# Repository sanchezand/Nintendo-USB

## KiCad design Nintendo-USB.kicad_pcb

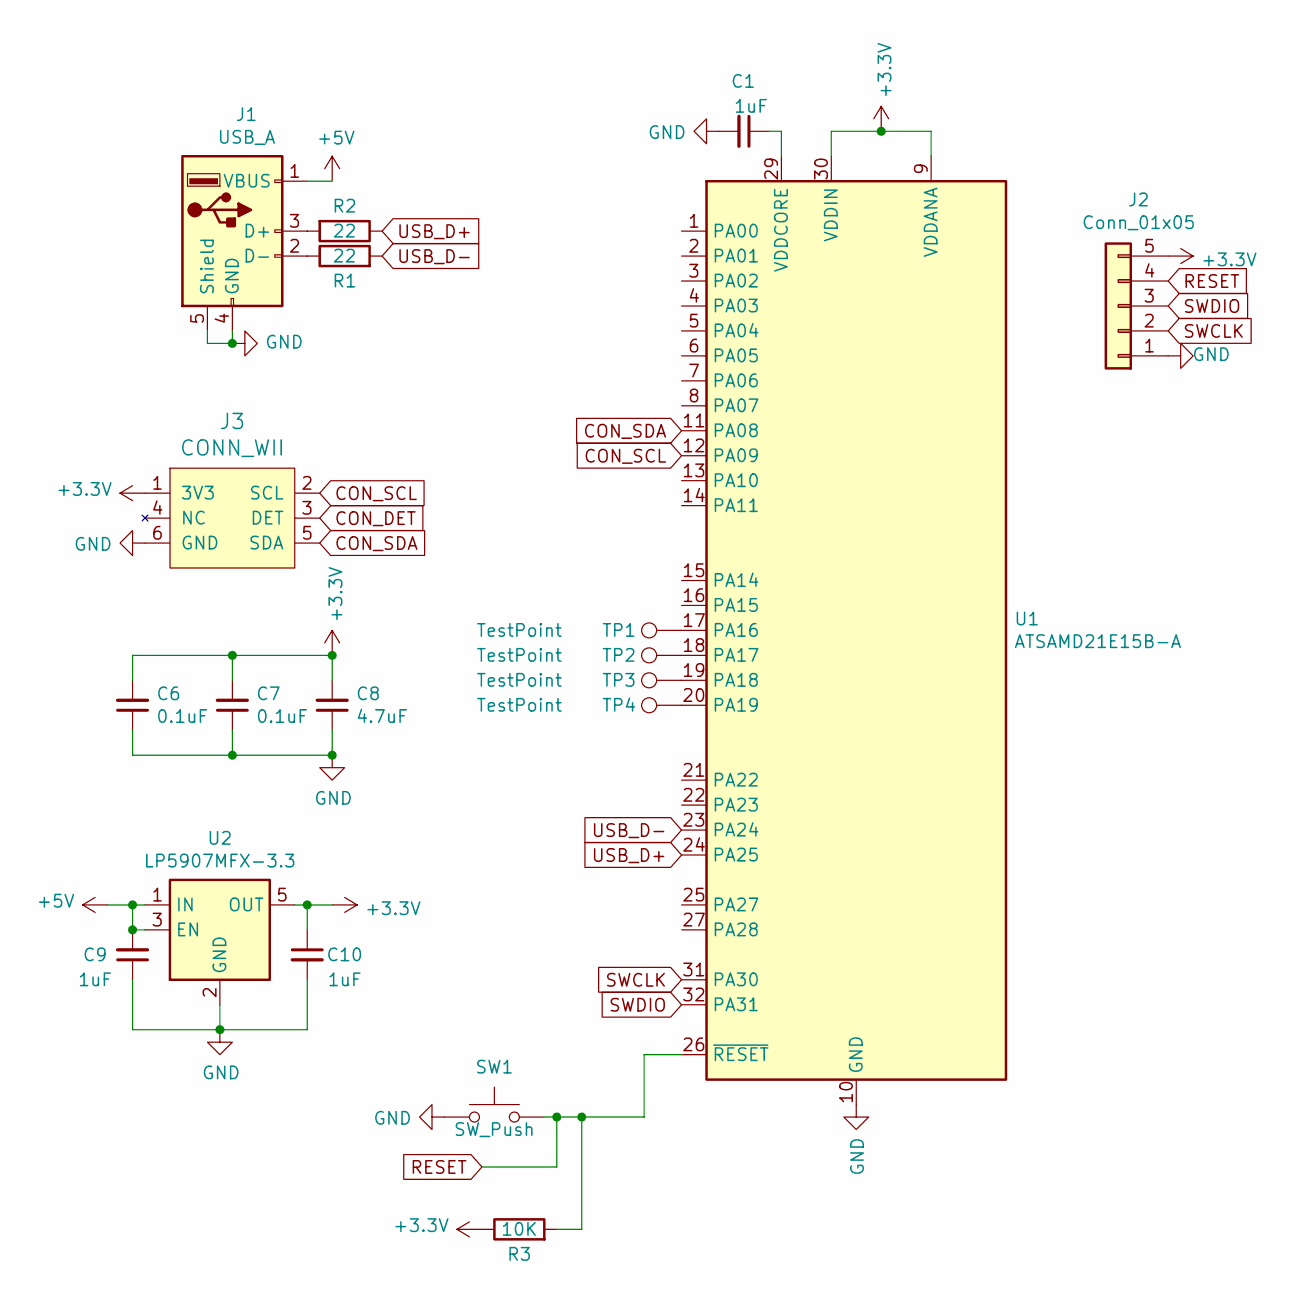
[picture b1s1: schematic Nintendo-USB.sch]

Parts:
C1, C9, C10: 1uF; C_0805_2012Metric_Pad1.18x1.45mm_HandSolder
C6, C7: 0.1uF; C_0805_2012Metric_Pad1.18x1.45mm_HandSolder
C8: 4.7uF; C_0805_2012Metric_Pad1.18x1.45mm_HandSolder
J1: USB_A; SOFNG-USB-07
J2: Conn_01x05; PinHeader_2x03_P2.00mm_Vertical
J3: CONN_WII
R1, R2: 22; R_0805_2012Metric_Pad1.20x1.40mm_HandSolder
R3: 10K; R_0805_2012Metric_Pad1.20x1.40mm_HandSolder
SW1: SW_Push; XKB-TS-1185EC-C-D-B
TP1, TP2, TP3, TP4: TestPoint; TestPoint_Pad_D1.0mm
U1: ATSAMD21E15B-A; TQFP-32_7x7mm_P0.8mm
U2: LP5907MFX-3.3; SOT-23-5

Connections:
+3V3: C6.2, C7.2, C8.2, C10.1, J2.5, J3.1 (3V3), R3.1, U1.9 (VDDANA), U1.30 (VDDIN), U2.5 (OUT)
+5V: C9.2, J1.1 (VBUS), U2.1 (IN), U2.3 (EN)
CON_DET: J3.3 (DET)
CON_SCL: J3.2 (SCL), U1.12 (PA09)
CON_SDA: J3.5 (SDA), U1.11 (PA08)
GND: C1.2, C6.1, C7.1, C8.1, C9.1, C10.2, J1.4 (GND), J1.5 (Shield), J2.1, J3.6 (GND), SW1.1, U1.10 (GND), U1.28 (GND), U2.2 (GND)
unnamed: C1.1, U1.29 (VDDCORE)
unnamed: J1.2 (D-), R1.1
unnamed: J1.3 (D+), R2.2
unnamed: TP1.1, U1.17 (PA16)
unnamed: TP2.1, U1.18 (PA17)
unnamed: TP3.1, U1.19 (PA18)
unnamed: TP4.1, U1.20 (PA19)
RESET: J2.4, R3.2, SW1.2, U1.26 (~RESET)
SWCLK: J2.2, U1.31 (PA30)
SWDIO: J2.3, U1.32 (PA31)
USB_D+: R2.1, U1.24 (PA25)
USB_D-: R1.2, U1.23 (PA24)

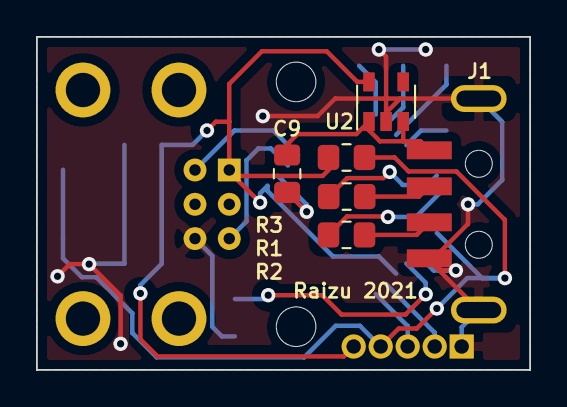
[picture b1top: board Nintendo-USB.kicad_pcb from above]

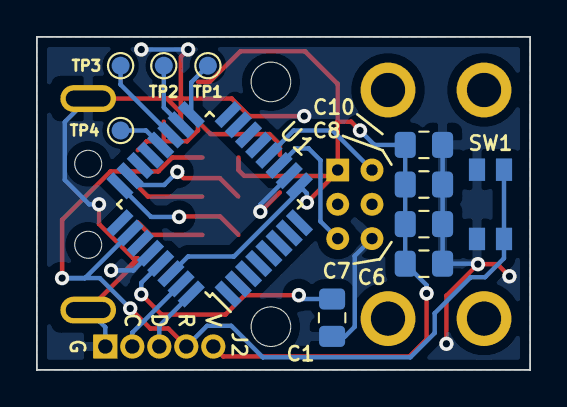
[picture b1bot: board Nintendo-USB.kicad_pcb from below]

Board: 2 copper layers, 27.4 x 18.5 mm, 19 parts (11 on the bottom side), 17 nets.

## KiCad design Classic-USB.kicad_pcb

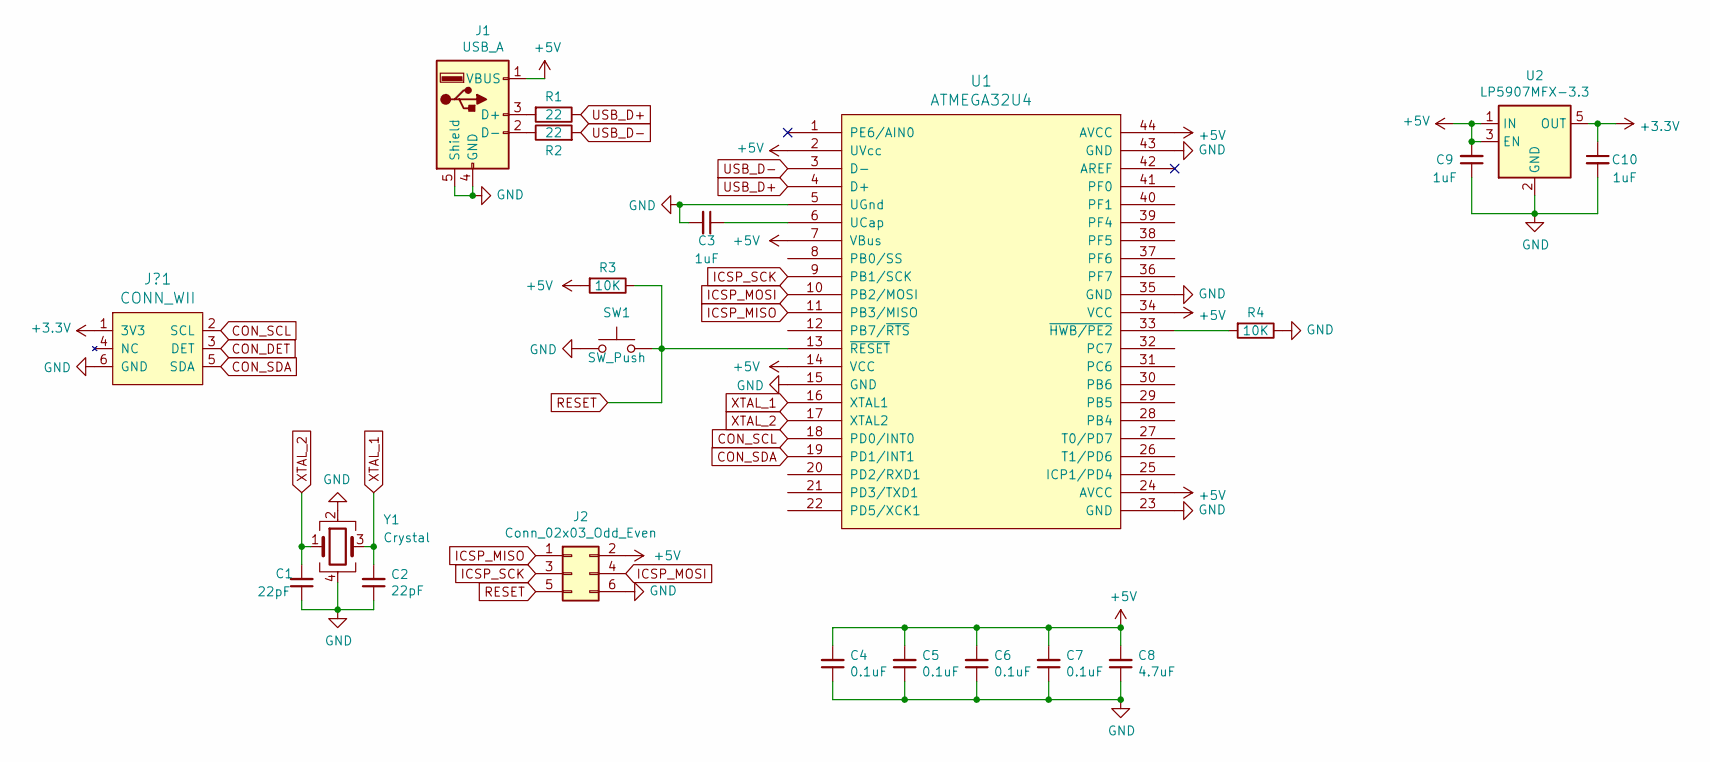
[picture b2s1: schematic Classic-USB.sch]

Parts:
C1, C2: 22pF; C_0805_2012Metric_Pad1.18x1.45mm_HandSolder
C3, C9, C10: 1uF; C_0805_2012Metric_Pad1.18x1.45mm_HandSolder
C4, C5, C6, C7: 0.1uF; C_0805_2012Metric_Pad1.18x1.45mm_HandSolder
C8: 4.7uF; C_0805_2012Metric_Pad1.18x1.45mm_HandSolder
J1: USB_A; SOFNG-USB-07
J2: Conn_02x03_Odd_Even; PinHeader_2x03_P2.54mm_Vertical
J?1: CONN_WII
R1, R2: 22; R_0805_2012Metric_Pad1.20x1.40mm_HandSolder
R3, R4: 10K; R_0805_2012Metric_Pad1.20x1.40mm_HandSolder
SW1: SW_Push; XKB-TS-1185EC-C-D-B
U1: ATMEGA32U4; TQFP-44_10x10mm_P0.8mm
U2: LP5907MFX-3.3; SOT-23-5
Y1: Crystal; Crystal_SMD_SeikoEpson_FA238-4Pin_3.2x2.5mm

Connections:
+3V3: C10.1, J?1.1 (3V3), U2.5 (OUT)
+5V: C4.2, C5.2, C6.2, C7.2, C8.2, C9.2, J1.1 (VBUS), J2.2, R3.2, U1.2 (UVcc), U1.7 (VBus), U1.14 (VCC), U1.24 (AVCC), U1.34 (VCC), U1.44 (AVCC), U2.1 (IN), U2.3 (EN)
CON_DET: J?1.3 (DET)
CON_SCL: J?1.2 (SCL), U1.18 (PD0/INT0)
CON_SDA: J?1.5 (SDA), U1.19 (PD1/INT1)
GND: C1.1, C2.1, C3.2, C4.1, C5.1, C6.1, C7.1, C8.1, C9.1, C10.2, J1.4 (GND), J1.5 (Shield), J2.6, J?1.6 (GND), R4.1, SW1.1, U1.5 (UGnd), U1.15 (GND), U1.23 (GND), U1.35 (GND), U1.43 (GND), U2.2 (GND), Y1.2, Y1.4
ICSP_MISO: J2.1, U1.11 (PB3/MISO)
ICSP_MOSI: J2.4, U1.10 (PB2/MOSI)
ICSP_SCK: J2.3, U1.9 (PB1/SCK)
unnamed: C3.1, U1.6 (UCap)
unnamed: J1.2 (D-), R2.1
unnamed: J1.3 (D+), R1.2
unnamed: R4.2, U1.33 (~HWB/PE2)
RESET: J2.5, R3.1, SW1.2, U1.13 (~RESET)
USB_D+: R1.1, U1.4 (D+)
USB_D-: R2.2, U1.3 (D-)
XTAL_1: C2.2, U1.16 (XTAL1), Y1.3
XTAL_2: C1.2, U1.17 (XTAL2), Y1.1

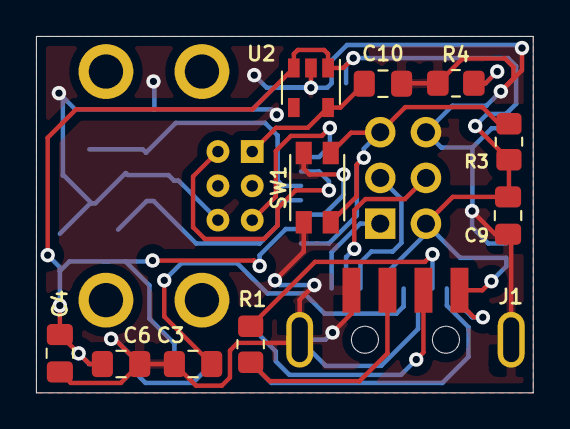
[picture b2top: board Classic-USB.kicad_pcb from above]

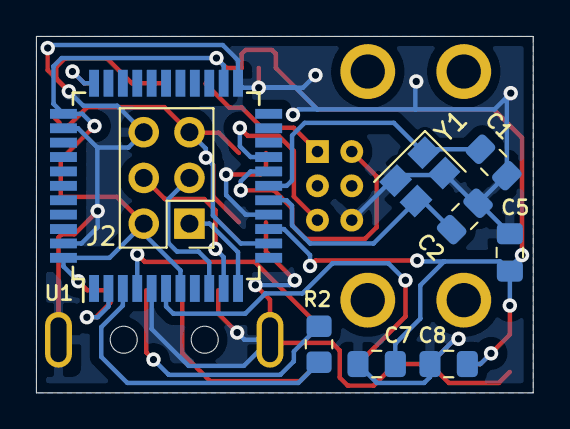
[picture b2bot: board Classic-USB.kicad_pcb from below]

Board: 2 copper layers, 27.6 x 19.8 mm, 21 parts (9 on the bottom side), 17 nets.

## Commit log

2021-08-10 Renamed files
2021-08-10 Version 2
